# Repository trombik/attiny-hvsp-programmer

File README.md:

# AVR High-voltage Serial Fuse Reprogrammer with Chip Erase function

Check out the full story behind this: [Removing a curse from ATtiny85 Fuses](https://blog.wokwi.com/removing-a-curse-from-attiny85-fuses).

If you want to make your own, take a look at [the wiring tutorial](https://www.hackster.io/sbinder/attiny85-powered-high-voltage-avr-programmer-3324e1).

## Schematic

## Requirements

* python 3 and [tox](https://tox.wiki/en/latest/install.html)

## Building

`tox.ini` install all the dependencies, including `platformio` and necessary
toolchains.

```console
tox
```

## Activating `tox` environment

In `tox` environment, you can run `platformio`.

```console
source .tox/python/bin/activate
```

```console
> pio --version
PlatformIO Core, version 6.1.3
```

To build, run:

```console
pio run
```

## Uploading the firmware

```console
pio run -t upload --upload-port ${SERIAL_PORT}
```

Replace `${SERIAL_PORT}` with the serial port on local machine.
`/dev/ttyUSB${N}` for Linux, `/dev/cuaU${N}` for FreeBSD, `COM${N}` for
Windows.

## License

License: GPL 3+

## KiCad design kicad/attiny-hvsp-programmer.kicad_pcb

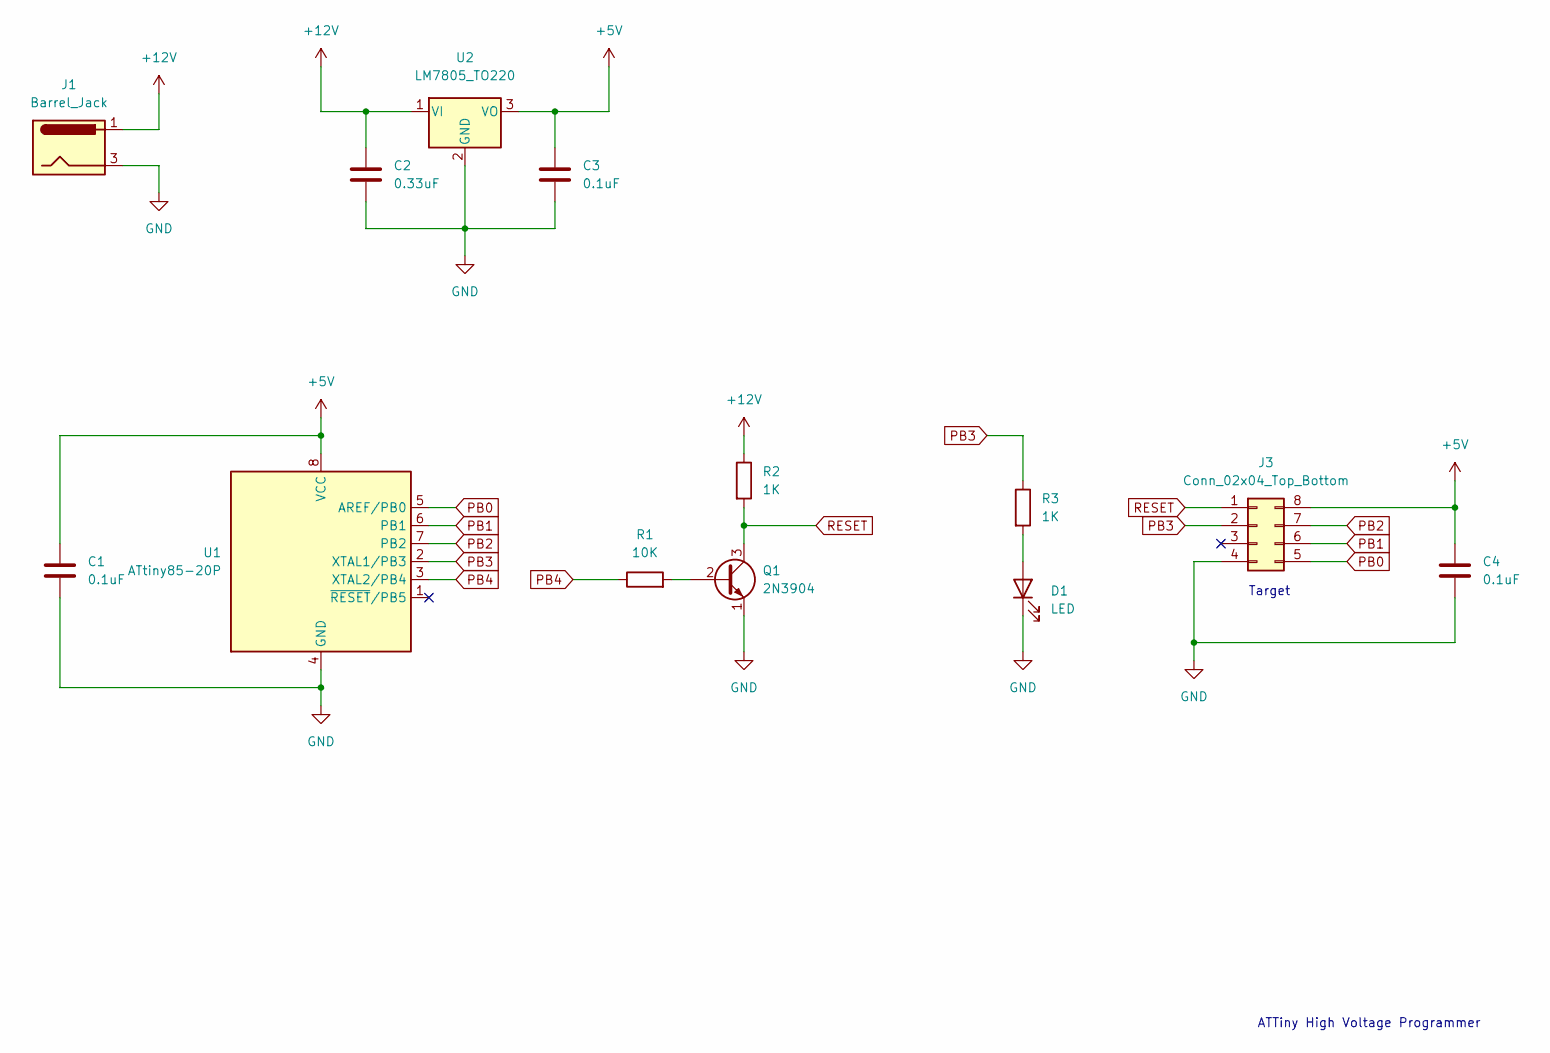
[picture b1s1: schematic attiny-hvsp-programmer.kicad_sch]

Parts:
C1, C3, C4: 0.1uF; C_Disc_D10.0mm_W2.5mm_P5.00mm
C2: 0.33uF; C_Disc_D10.0mm_W2.5mm_P5.00mm
D1: LED; LED_D3.0mm
J1: Barrel_Jack; PinHeader_1x03_P2.54mm_Vertical
J3: Conn_02x04_Top_Bottom; DIP-8_W7.62mm_Socket
Q1: 2N3904; TO-92_Inline_Wide
R1: 10K; R_Axial_DIN0207_L6.3mm_D2.5mm_P2.54mm_Vertical
R2: 1K; R_Axial_DIN0207_L6.3mm_D2.5mm_P7.62mm_Horizontal
R3: 1K; R_Axial_DIN0207_L6.3mm_D2.5mm_P5.08mm_Vertical
U1: ATtiny85-20P; DIP-8_W7.62mm
U2: LM7805_TO220; TO-220-3_Vertical

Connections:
+5V: C1.1, C3.1, C4.1, J3.8, U1.8 (VCC), U2.3 (VO)
+12V: C2.1, J1.1, R2.1, U2.1 (VI)
GND: C1.2, C2.2, C3.2, C4.2, D1.1 (K), J1.3, J3.4, Q1.1 (E), U1.4 (GND), U2.2 (GND)
unnamed: D1.2 (A), R3.2
unnamed: Q1.2 (B), R1.2
PB0: J3.5, U1.5 (AREF/PB0)
PB1: J3.6, U1.6 (PB1)
PB2: J3.7, U1.7 (PB2)
PB3: J3.2, R3.1, U1.2 (XTAL1/PB3)
PB4: R1.1, U1.3 (XTAL2/PB4)
RESET: J3.1, Q1.3 (C), R2.2

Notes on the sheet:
ATTiny High Voltage Programmer
Target

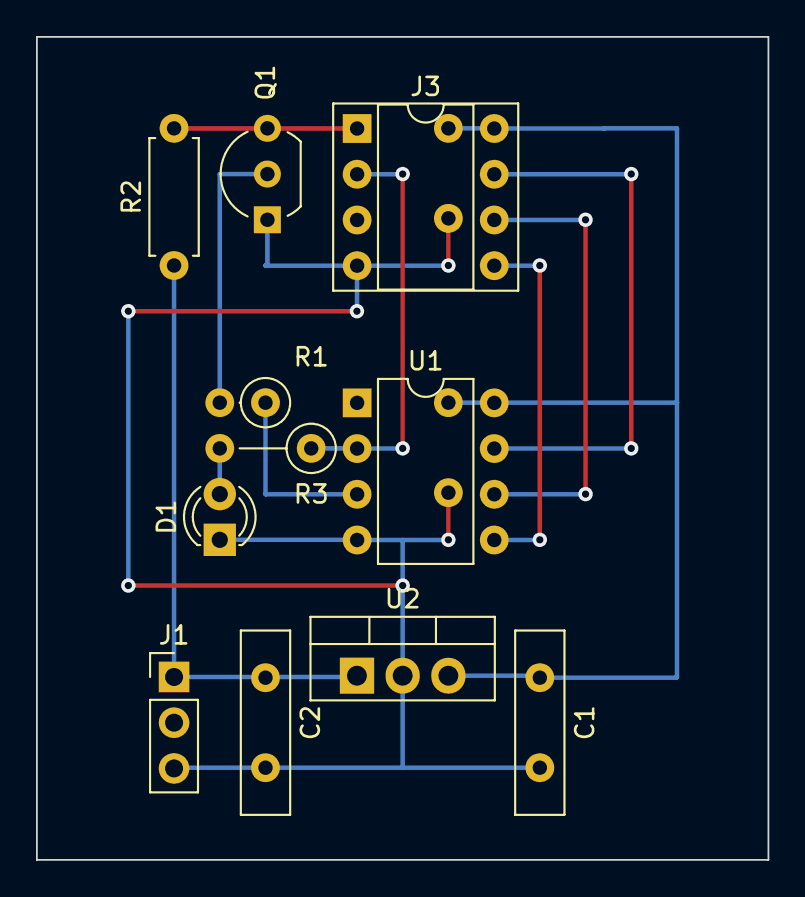
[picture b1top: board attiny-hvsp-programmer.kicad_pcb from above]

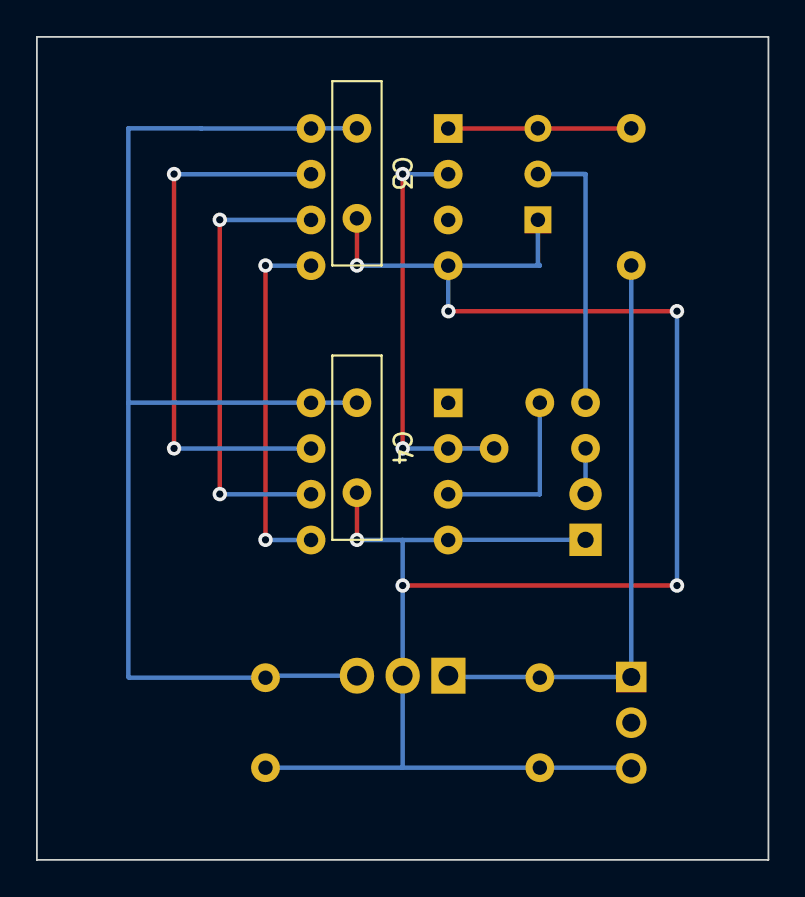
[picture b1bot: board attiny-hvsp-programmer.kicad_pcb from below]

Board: 2 copper layers, 40.6 x 45.7 mm, 13 parts (2 on the bottom side), 11 nets.

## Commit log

2022-07-28 feat: add kicad project
2022-07-28 doc: add schematic
2022-07-28 feat: use platformio as a build system
2022-07-28 bugfix: sync footprints
2022-07-28 bugfix: add edge-cut
2022-07-28 doc: add LICENSE
